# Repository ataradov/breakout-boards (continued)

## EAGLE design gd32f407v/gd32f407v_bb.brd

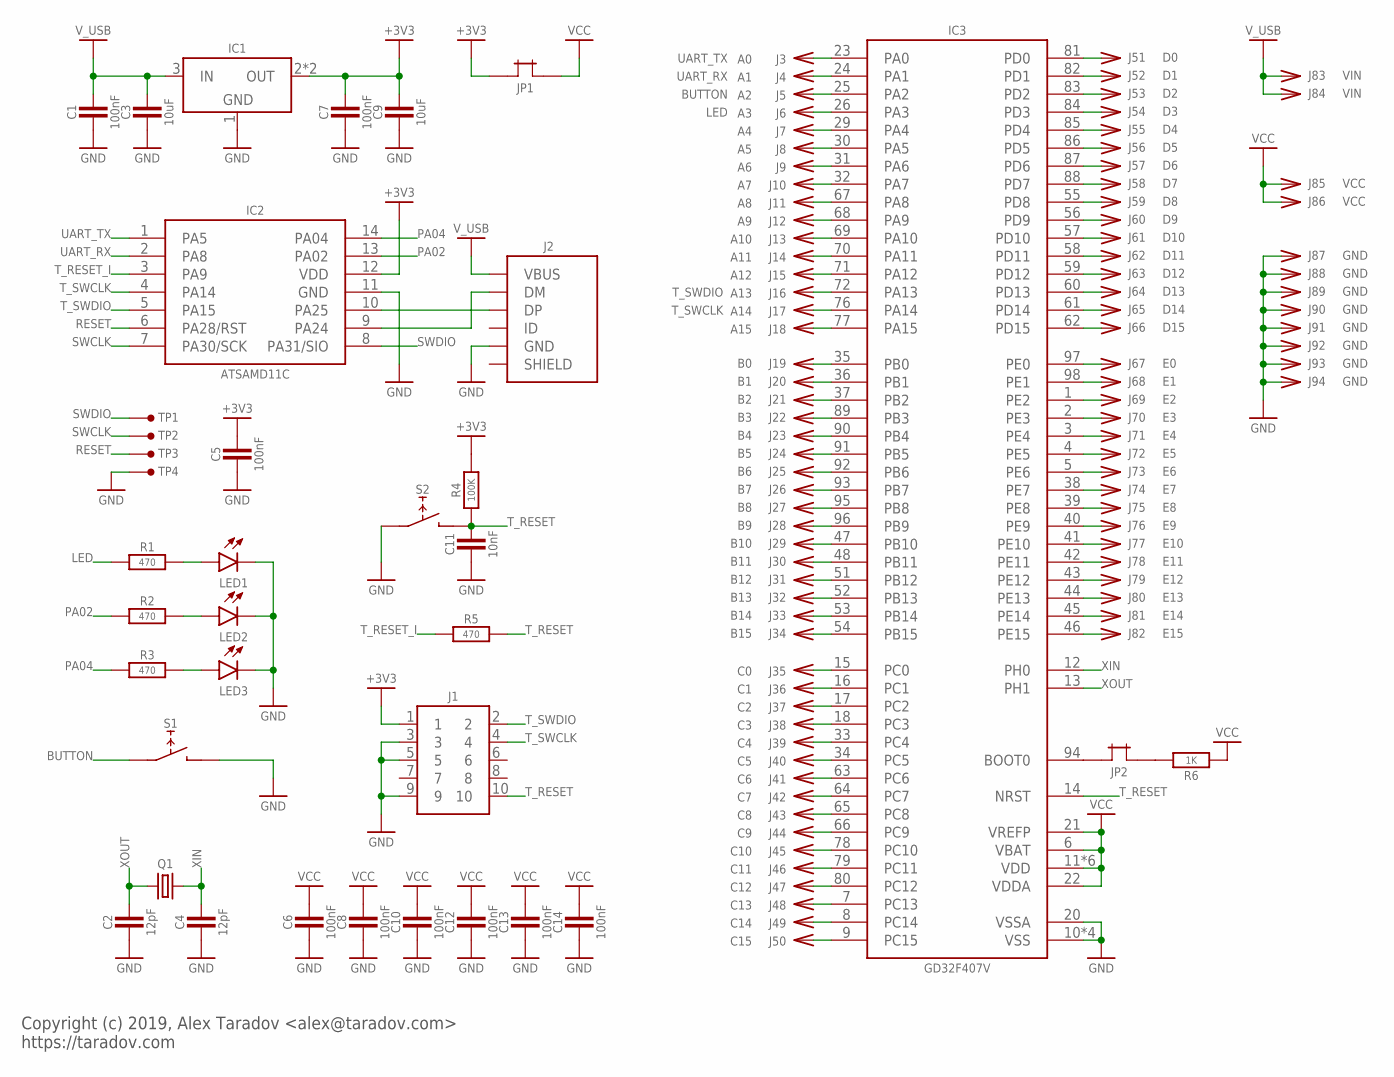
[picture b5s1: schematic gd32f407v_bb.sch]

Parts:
C1, C5, C6, C7, C8, C10, C12, C13, C14: 100nF; SMD0603
C2, C4: 12pF; SMD0603
C3, C9: 10uF; SMD0805
C11: 10nF; SMD0603
IC1: LM1117-SOT223; SOT223
IC2: ATSAMD11C; SO-14
IC3: GD32F407V; TQFP-100-0.5MM
J1: HEADER-5X2-TH-1.27; HEADER-5X2-1.27MM
J2: USB-B-MICRO-SMT; USB-B-MICRO-SMT-SHELL-TH
J3: A0; PIN-TH
J4: A1; PIN-TH
J5: A2; PIN-TH
J6: A3; PIN-TH
J7: A4; PIN-TH
J8: A5; PIN-TH
J9: A6; PIN-TH
J10: A7; PIN-TH
J11: A8; PIN-TH
J12: A9; PIN-TH
J13: A10; PIN-TH
J14: A11; PIN-TH
J15: A12; PIN-TH
J16: A13; PIN-TH
J17: A14; PIN-TH
J18: A15; PIN-TH
J19: B0; PIN-TH
J20: B1; PIN-TH
J21: B2; PIN-TH
J22: B3; PIN-TH
J23: B4; PIN-TH
J24: B5; PIN-TH
J25: B6; PIN-TH
J26: B7; PIN-TH
J27: B8; PIN-TH
J28: B9; PIN-TH
J29: B10; PIN-TH
J30: B11; PIN-TH
J31: B12; PIN-TH
J32: B13; PIN-TH
J33: B14; PIN-TH
J34: B15; PIN-TH
J35: C0; PIN-TH
J36: C1; PIN-TH
J37: C2; PIN-TH
J38: C3; PIN-TH
J39: C4; PIN-TH
J40: C5; PIN-TH
J41: C6; PIN-TH
J42: C7; PIN-TH
J43: C8; PIN-TH
J44: C9; PIN-TH
J45: C10; PIN-TH
J46: C11; PIN-TH
J47: C12; PIN-TH
J48: C13; PIN-TH
J49: C14; PIN-TH
J50: C15; PIN-TH
J51: D0; PIN-TH
J52: D1; PIN-TH
J53: D2; PIN-TH
J54: D3; PIN-TH
J55: D4; PIN-TH
J56: D5; PIN-TH
J57: D6; PIN-TH
J58: D7; PIN-TH
J59: D8; PIN-TH
J60: D9; PIN-TH
J61: D10; PIN-TH
J62: D11; PIN-TH
J63: D12; PIN-TH
J64: D13; PIN-TH
J65: D14; PIN-TH
J66: D15; PIN-TH
J67: E0; PIN-TH
J68: E1; PIN-TH
J69: E2; PIN-TH
J70: E3; PIN-TH
J71: E4; PIN-TH
J72: E5; PIN-TH
J73: E6; PIN-TH
J74: E7; PIN-TH
J75: E8; PIN-TH
J76: E9; PIN-TH
J77: E10; PIN-TH
J78: E11; PIN-TH
J79: E12; PIN-TH
J80: E13; PIN-TH
J81: E14; PIN-TH
J82: E15; PIN-TH
J83, J84: VIN; PIN-TH
J85, J86: VCC; PIN-TH
J87, J88, J89, J90, J91, J92, J93, J94: GND; PIN-TH
JP1, JP2: JUMPER-TH-TH; JUMPER-TH
LED1, LED2, LED3: LED_SMDLED_0603; SMD0603
Q1: XTAL-CTS406; CTS406
R1, R2, R3, R5: 470; SMD0603
R4: 100K; SMD0603
R6: 1K; SMD0603
S1, S2: TACT_SWITCH_6MM-SMD-HALF; TACT-SMD-6MM-HALF
TP1: SIO; TP-1.27MM
TP2, TP3, TP4: TEST-POINT-1.27MM; TP-1.27MM

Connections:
+3V3: C5.2, C7.2, C9.2, IC1.2 (OUT), IC1.4 (OUT), IC2.12 (VDD), J1.1, JP1.1, R4.2
BUTTON: IC3.25 (PA2), J5.1, S1.1
GND: C1.1, C2.1, C3.1, C4.1, C5.1, C6.1, C7.1, C8.1, C9.1, C10.1, C11.1, C12.1, C13.1, C14.1, IC1.1 (GND), IC2.11 (GND), IC3.10 (VSS), IC3.20 (VSSA), IC3.27 (VSS), IC3.74 (VSS), IC3.99 (VSS), J1.3, J1.5, J1.9, J2.5 (GND), J87.1, J88.1, J89.1, J90.1, J91.1, J92.1, J93.1, J94.1, LED1.2 (C), LED2.2 (C), LED3.2 (C), S1.2, S2.1, TP4.1
LED: IC3.26 (PA3), J6.1, R1.1
unnamed: IC2.9 (PA24), J2.2 (DM)
unnamed: IC2.10 (PA25), J2.3 (DP)
unnamed: LED2.1 (A), R2.2
unnamed: LED3.1 (A), R3.2
unnamed: IC3.29 (PA4), J7.1
unnamed: IC3.30 (PA5), J8.1
unnamed: IC3.31 (PA6), J9.1
unnamed: IC3.32 (PA7), J10.1
unnamed: IC3.67 (PA8), J11.1
unnamed: IC3.68 (PA9), J12.1
unnamed: IC3.69 (PA10), J13.1
unnamed: IC3.70 (PA11), J14.1
unnamed: IC3.71 (PA12), J15.1
unnamed: IC3.77 (PA15), J18.1
unnamed: IC3.81 (PD0), J51.1
unnamed: IC3.82 (PD1), J52.1
unnamed: IC3.83 (PD2), J53.1
unnamed: IC3.84 (PD3), J54.1
unnamed: IC3.85 (PD4), J55.1
unnamed: IC3.86 (PD5), J56.1
unnamed: IC3.87 (PD6), J57.1
unnamed: IC3.88 (PD7), J58.1
unnamed: IC3.55 (PD8), J59.1
unnamed: IC3.56 (PD9), J60.1
unnamed: IC3.57 (PD10), J61.1
unnamed: IC3.58 (PD11), J62.1
unnamed: IC3.59 (PD12), J63.1
unnamed: IC3.60 (PD13), J64.1
unnamed: IC3.61 (PD14), J65.1
unnamed: IC3.62 (PD15), J66.1
unnamed: IC3.35 (PB0), J19.1
unnamed: IC3.36 (PB1), J20.1
unnamed: IC3.37 (PB2), J21.1
unnamed: IC3.89 (PB3), J22.1
unnamed: IC3.90 (PB4), J23.1
unnamed: IC3.91 (PB5), J24.1
unnamed: IC3.92 (PB6), J25.1
unnamed: IC3.93 (PB7), J26.1
unnamed: IC3.95 (PB8), J27.1
unnamed: IC3.96 (PB9), J28.1
unnamed: IC3.47 (PB10), J29.1
unnamed: IC3.48 (PB11), J30.1
unnamed: IC3.51 (PB12), J31.1
unnamed: LED1.1 (A), R1.2
unnamed: IC3.52 (PB13), J32.1
unnamed: IC3.53 (PB14), J33.1
unnamed: IC3.54 (PB15), J34.1
unnamed: IC3.97 (PE0), J67.1
unnamed: IC3.98 (PE1), J68.1
unnamed: IC3.1 (PE2), J69.1
unnamed: IC3.2 (PE3), J70.1
unnamed: IC3.3 (PE4), J71.1
unnamed: IC3.4 (PE5), J72.1
unnamed: IC3.5 (PE6), J73.1
unnamed: IC3.38 (PE7), J74.1
unnamed: IC3.39 (PE8), J75.1
unnamed: IC3.40 (PE9), J76.1
unnamed: IC3.41 (PE10), J77.1
unnamed: IC3.42 (PE11), J78.1
unnamed: IC3.43 (PE12), J79.1
unnamed: IC3.44 (PE13), J80.1
unnamed: IC3.45 (PE14), J81.1
unnamed: IC3.46 (PE15), J82.1
unnamed: IC3.15 (PC0), J35.1
unnamed: IC3.16 (PC1), J36.1
unnamed: IC3.17 (PC2), J37.1
unnamed: IC3.18 (PC3), J38.1
unnamed: IC3.33 (PC4), J39.1
unnamed: IC3.34 (PC5), J40.1
unnamed: IC3.63 (PC6), J41.1
unnamed: IC3.64 (PC7), J42.1
unnamed: IC3.65 (PC8), J43.1
unnamed: IC3.66 (PC9), J44.1
unnamed: IC3.78 (PC10), J45.1
unnamed: IC3.79 (PC11), J46.1
unnamed: IC3.80 (PC12), J47.1
unnamed: IC3.7 (PC13), J48.1
unnamed: IC3.8 (PC14), J49.1
unnamed: IC3.9 (PC15), J50.1
unnamed: IC3.94 (BOOT0), JP2.1
unnamed: JP2.2, R6.2
PA02: IC2.13 (PA02), R2.1
PA04: IC2.14 (PA04), R3.1
RESET: IC2.6 (PA28/RST), TP3.1
SWCLK: IC2.7 (PA30/SCK), TP2.1
SWDIO: IC2.8 (PA31/SIO), TP1.1
T_RESET: C11.2, IC3.14 (NRST), J1.10, R4.1, R5.2, S2.2
T_RESET_I: IC2.3 (PA9), R5.1
T_SWCLK: IC2.4 (PA14), IC3.76 (PA14), J1.4, J17.1
T_SWDIO: IC2.5 (PA15), IC3.72 (PA13), J1.2, J16.1
UART_RX: IC2.2 (PA8), IC3.24 (PA1), J4.1
UART_TX: IC2.1 (PA5), IC3.23 (PA0), J3.1
VCC: C6.2, C8.2, C10.2, C12.2, C13.2, C14.2, IC3.6 (VBAT), IC3.11 (VDD), IC3.19 (VDD), IC3.21 (VREFP), IC3.22 (VDDA), IC3.28 (VDD), IC3.50 (VDD), IC3.75 (VDD), IC3.100 (VDD), J85.1, J86.1, JP1.2, R6.1
V_USB: C1.2, C3.2, IC1.3 (IN), J2.1 (VBUS), J83.1, J84.1
XIN: C4.2, IC3.12 (PH0), Q1.3 (2)
XOUT: C2.2, IC3.13 (PH1), Q1.1

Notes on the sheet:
Copyright (c) 2019, Alex Taradov <alex@taradov.com> https://taradov.com

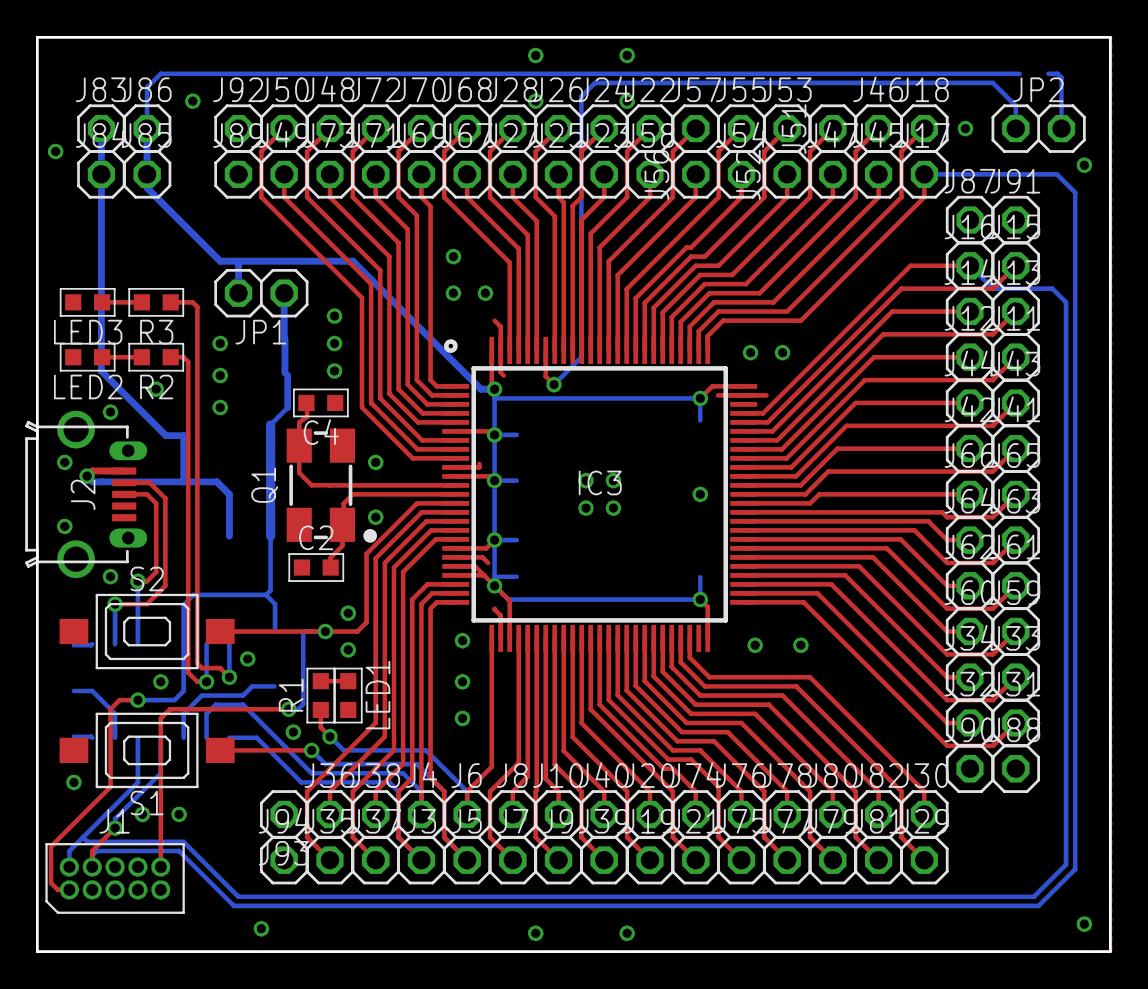
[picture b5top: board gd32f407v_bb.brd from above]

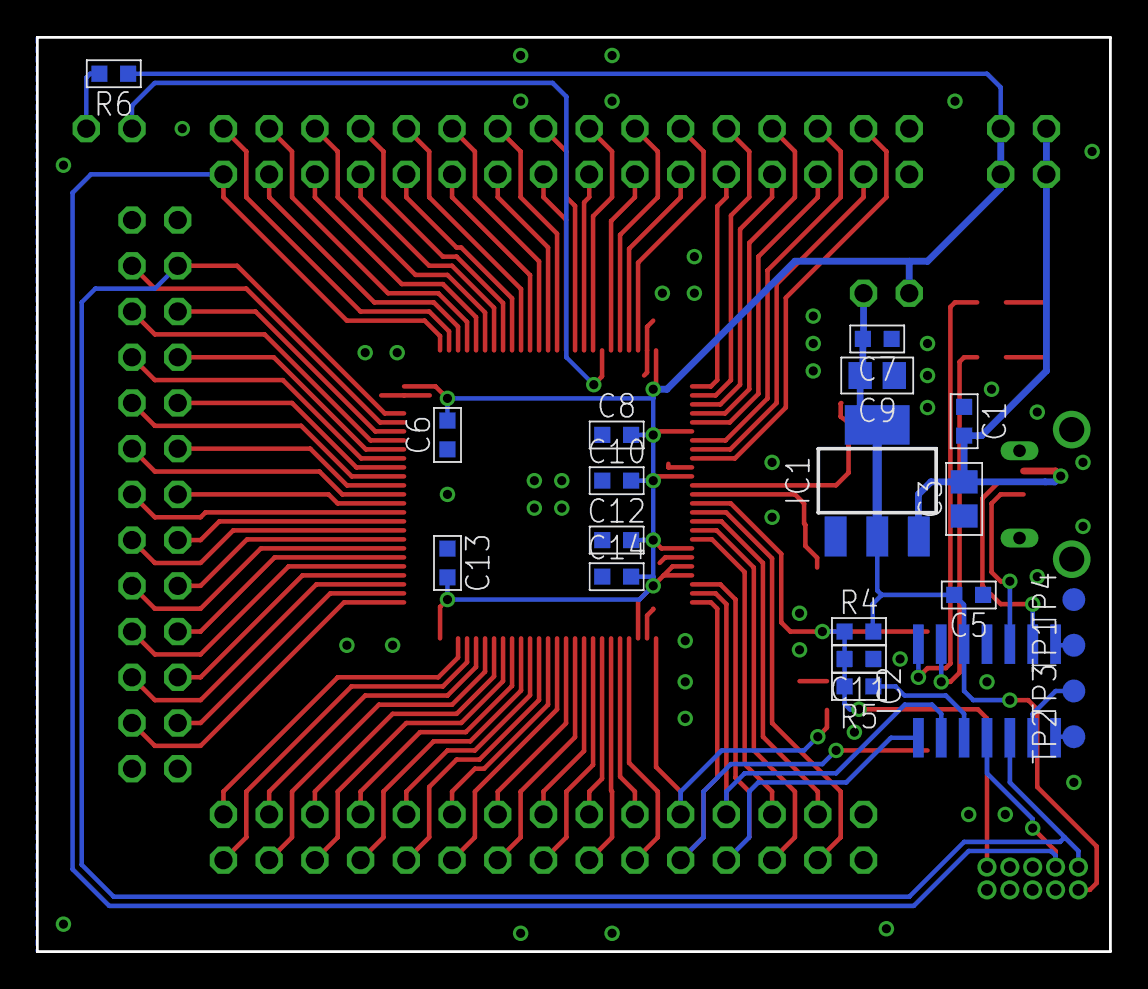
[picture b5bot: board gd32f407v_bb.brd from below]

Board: 2 copper layers, 59.6 x 50.8 mm, 129 parts (21 on the bottom side), 100 nets.

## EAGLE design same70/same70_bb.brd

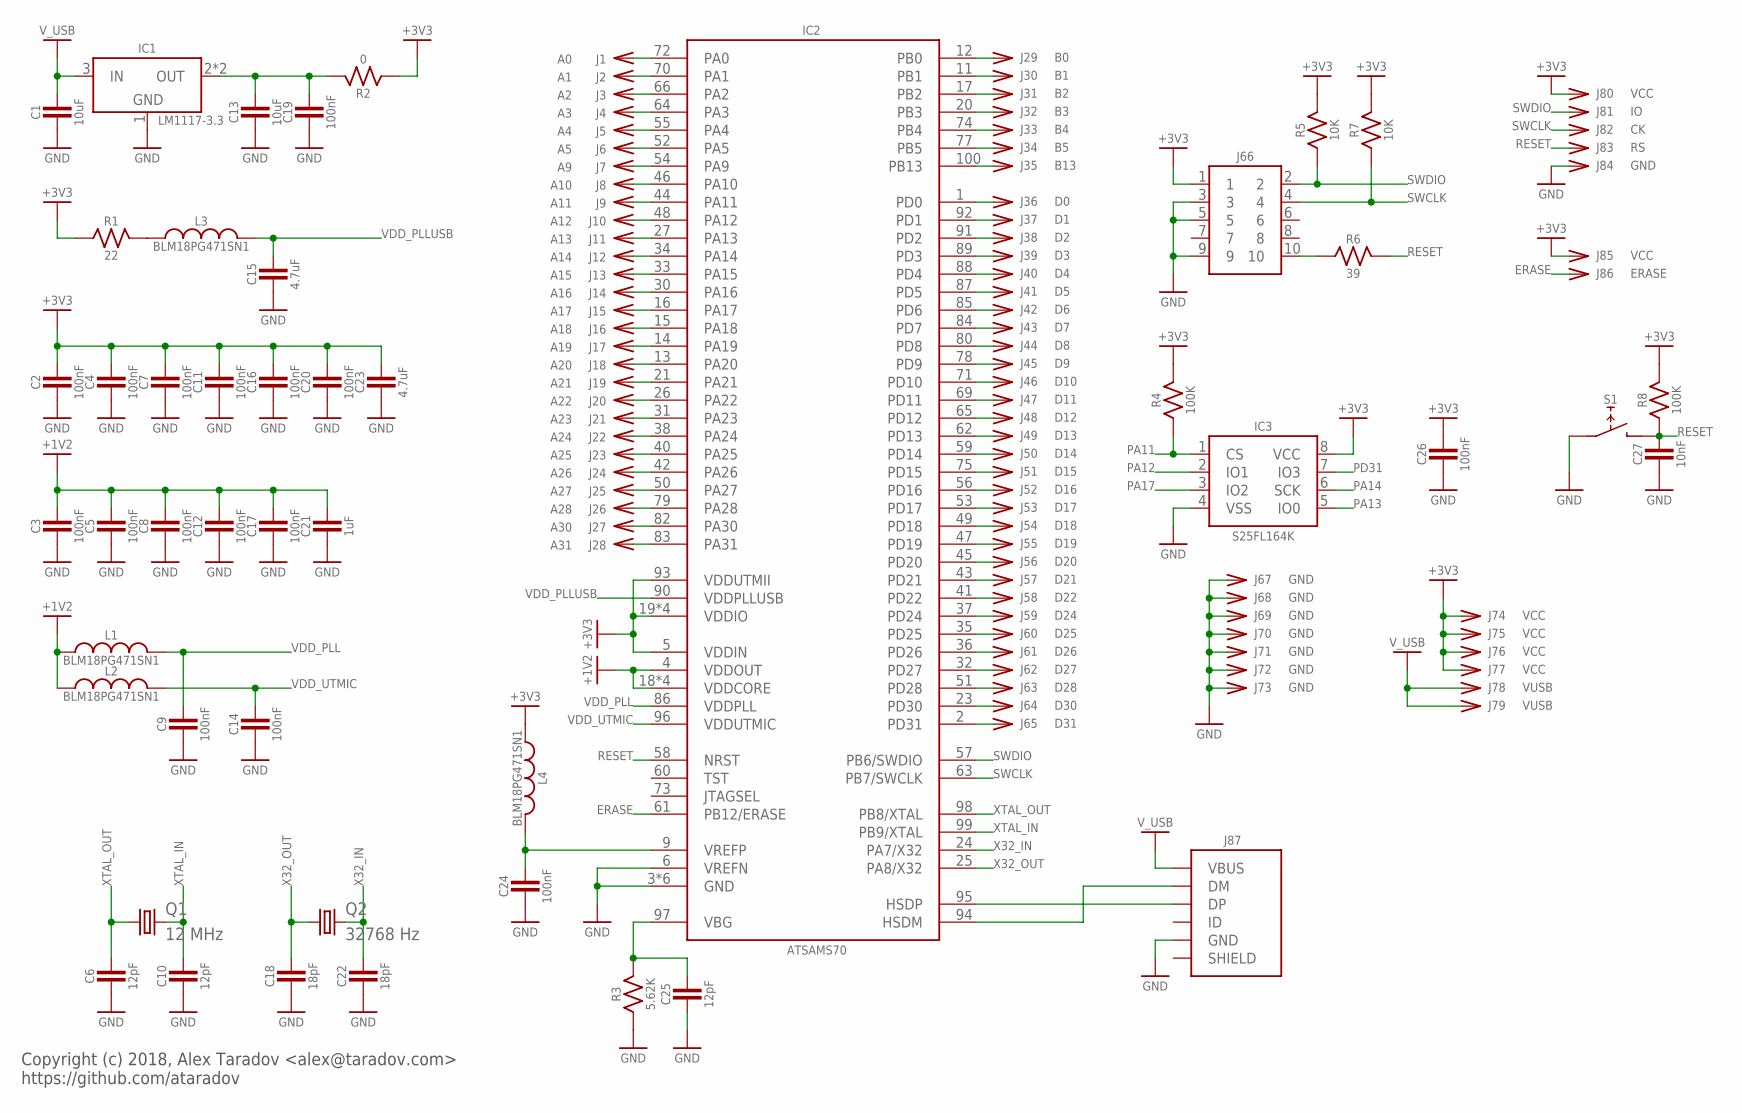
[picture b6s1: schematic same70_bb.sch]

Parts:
C1, C13: 10uF; SMD0805
C2, C3, C4, C5, C7, C8, C9, C11, C12, C14, C16, C17, C19, C20, C24, C26: 100nF; SMD0603
C6, C10, C25: 12pF; SMD0603
C15, C23: 4.7uF; SMD0603
C18, C22: 18pF; SMD0603
C21: 1uF; SMD0603
C27: 10nF; SMD0603
IC1: LM1117-3.3; SOT223
IC2: ATSAMS70; TQFP-100-0.5MM
IC3: S25FL164K; SO8
J1: A0; PIN-TH
J2: A1; PIN-TH
J3: A2; PIN-TH
J4: A3; PIN-TH
J5: A4; PIN-TH
J6: A5; PIN-TH
J7: A9; PIN-TH
J8: A10; PIN-TH
J9: A11; PIN-TH
J10: A12; PIN-TH
J11: A13; PIN-TH
J12: A14; PIN-TH
J13: A15; PIN-TH
J14: A16; PIN-TH
J15: A17; PIN-TH
J16: A18; PIN-TH
J17: A19; PIN-TH
J18: A20; PIN-TH
J19: A21; PIN-TH
J20: A22; PIN-TH
J21: A23; PIN-TH
J22: A24; PIN-TH
J23: A25; PIN-TH
J24: A26; PIN-TH
J25: A27; PIN-TH
J26: A28; PIN-TH
J27: A30; PIN-TH
J28: A31; PIN-TH
J29: B0; PIN-TH
J30: B1; PIN-TH
J31: B2; PIN-TH
J32: B3; PIN-TH
J33: B4; PIN-TH
J34: B5; PIN-TH
J35: B13; PIN-TH
J36: D0; PIN-TH
J37: D1; PIN-TH
J38: D2; PIN-TH
J39: D3; PIN-TH
J40: D4; PIN-TH
J41: D5; PIN-TH
J42: D6; PIN-TH
J43: D7; PIN-TH
J44: D8; PIN-TH
J45: D9; PIN-TH
J46: D10; PIN-TH
J47: D11; PIN-TH
J48: D12; PIN-TH
J49: D13; PIN-TH
J50: D14; PIN-TH
J51: D15; PIN-TH
J52: D16; PIN-TH
J53: D17; PIN-TH
J54: D18; PIN-TH
J55: D19; PIN-TH
J56: D20; PIN-TH
J57: D21; PIN-TH
J58: D22; PIN-TH
J59: D24; PIN-TH
J60: D25; PIN-TH
J61: D26; PIN-TH
J62: D27; PIN-TH
J63: D28; PIN-TH
J64: D30; PIN-TH
J65: D31; PIN-TH
J66: HEADER-5X2-TH-1.27; HEADER-5X2-1.27MM
J67, J68, J69, J70, J71, J72, J73, J84: GND; PIN-TH
J74, J75, J76, J77, J80, J85: VCC; PIN-TH
J78, J79: VUSB; PIN-TH
J81: IO; PIN-TH
J82: CK; PIN-TH
J83: RS; PIN-TH
J86: ERASE; PIN-TH
J87: USB-B-MICRO-SMT; USB-B-MICRO-SMT-SHELL-TH
L1, L2, L3, L4: BLM18PG471SN1; SMD0603
Q1: 12 MHz; CTS406
Q2: 32768 Hz; TC38H
R1: 22; SMD0603
R2: 0; SMD0603
R3: 5.62K; SMD0603
R4, R8: 100K; SMD0603
R5, R7: 10K; SMD0603
R6: 39; SMD0603
S1: TACT_SWITCH_6MM-SMD; TACT-SMD-6MM

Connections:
+1V2: C3.2, C5.2, C8.2, C12.2, C17.2, C21.2, IC2.4 (VDDOUT), IC2.18 (VDDCORE), IC2.22 (VDDCORE), IC2.39 (VDDCORE), IC2.76 (VDDCORE), L1.1, L2.1
+3V3: C2.2, C4.2, C7.2, C11.2, C16.2, C20.2, C23.2, C26.2, IC2.5 (VDDIN), IC2.19 (VDDIO), IC2.28 (VDDIO), IC2.68 (VDDIO), IC2.81 (VDDIO), IC2.93 (VDDUTMII), IC3.8 (VCC), J66.1, J74.1, J75.1, J76.1, J77.1, J80.1, J85.1, L4.1, R1.1, R2.1, R4.2, R5.2, R7.2, R8.2
ERASE: IC2.61 (PB12/ERASE), J86.1
GND: C1.1, C2.1, C3.1, C4.1, C5.1, C6.1, C7.1, C8.1, C9.1, C10.1, C11.1, C12.1, C13.1, C14.1, C15.1, C16.1, C17.1, C18.1, C19.1, C20.1, C21.1, C22.1, C23.1, C24.1, C25.1, C26.1, C27.1, IC1.1 (GND), IC2.3 (GND), IC2.6 (VREFN), IC2.7 (GND), IC2.8 (GND), IC2.10 (GND), IC2.29 (GND), IC2.67 (GND), IC3.4 (VSS), J66.3, J66.5, J66.9, J67.1, J68.1, J69.1, J70.1, J71.1, J72.1, J73.1, J84.1, J87.5 (GND), R3.1, S1.1, S1.2 (1)
unnamed: IC2.45 (PD20), J56.1
unnamed: J66.10, R6.1
unnamed: IC2.12 (PB0), J29.1
unnamed: IC2.11 (PB1), J30.1
unnamed: IC2.17 (PB2), J31.1
unnamed: IC2.20 (PB3), J32.1
unnamed: IC2.74 (PB4), J33.1
unnamed: IC2.77 (PB5), J34.1
unnamed: IC2.89 (PD3), J39.1
unnamed: IC2.47 (PD19), J55.1
unnamed: IC2.49 (PD18), J54.1
unnamed: IC2.53 (PD17), J53.1
unnamed: IC2.100 (PB13), J35.1
unnamed: IC2.1 (PD0), J36.1
unnamed: IC2.92 (PD1), J37.1
unnamed: IC2.91 (PD2), J38.1
unnamed: IC2.56 (PD16), J52.1
unnamed: IC2.75 (PD15), J51.1
unnamed: IC2.59 (PD14), J50.1
unnamed: IC2.62 (PD13), J49.1
unnamed: IC2.65 (PD12), J48.1
unnamed: IC2.69 (PD11), J47.1
unnamed: IC2.71 (PD10), J46.1
unnamed: IC2.78 (PD9), J45.1
unnamed: IC2.80 (PD8), J44.1
unnamed: IC2.84 (PD7), J43.1
unnamed: IC2.23 (PD30), J64.1
unnamed: IC2.51 (PD28), J63.1
unnamed: IC2.32 (PD27), J62.1
unnamed: IC2.36 (PD26), J61.1
unnamed: IC2.35 (PD25), J60.1
unnamed: IC2.37 (PD24), J59.1
unnamed: IC2.41 (PD22), J58.1
unnamed: IC2.43 (PD21), J57.1
unnamed: IC2.85 (PD6), J42.1
unnamed: IC2.72 (PA0), J1.1
unnamed: IC2.70 (PA1), J2.1
unnamed: IC2.66 (PA2), J3.1
unnamed: IC2.64 (PA3), J4.1
unnamed: IC2.55 (PA4), J5.1
unnamed: IC2.52 (PA5), J6.1
unnamed: IC2.54 (PA9), J7.1
unnamed: IC2.46 (PA10), J8.1
unnamed: IC2.88 (PD4), J40.1
unnamed: IC2.87 (PD5), J41.1
unnamed: IC2.33 (PA15), J13.1
unnamed: IC2.30 (PA16), J14.1
unnamed: IC2.15 (PA18), J16.1
unnamed: IC2.14 (PA19), J17.1
unnamed: IC2.13 (PA20), J18.1
unnamed: IC2.21 (PA21), J19.1
unnamed: IC2.26 (PA22), J20.1
unnamed: IC2.31 (PA23), J21.1
unnamed: IC2.38 (PA24), J22.1
unnamed: IC2.42 (PA26), J24.1
unnamed: IC2.50 (PA27), J25.1
unnamed: IC2.79 (PA28), J26.1
unnamed: IC2.82 (PA30), J27.1
unnamed: IC2.83 (PA31), J28.1
unnamed: IC2.40 (PA25), J23.1
unnamed: C25.2, IC2.97 (VBG), R3.2
unnamed: IC2.94 (HSDM), J87.2 (DM)
unnamed: C24.2, IC2.9 (VREFP), L4.2
unnamed: C13.2, C19.2, IC1.2 (OUT), IC1.4 (OUT), R2.2
unnamed: IC2.95 (HSDP), J87.3 (DP)
unnamed: L3.1, R1.2
PA11: IC2.44 (PA11), IC3.1 (CS), J9.1, R4.1
PA12: IC2.48 (PA12), IC3.2 (IO1), J10.1
PA13: IC2.27 (PA13), IC3.5 (IO0), J11.1
PA14: IC2.34 (PA14), IC3.6 (SCK), J12.1
PA17: IC2.16 (PA17), IC3.3 (IO2), J15.1
PD31: IC2.2 (PD31), IC3.7 (IO3), J65.1
RESET: C27.2, IC2.58 (NRST), J83.1, R6.2, R8.1, S1.3 (2), S1.4 (2)
SWCLK: IC2.63 (PB7/SWCLK), J66.4, J82.1, R7.1
SWDIO: IC2.57 (PB6/SWDIO), J66.2, J81.1, R5.1
VDD_PLL: C9.2, IC2.86 (VDDPLL), L1.2
VDD_PLLUSB: C15.2, IC2.90 (VDDPLLUSB), L3.2
VDD_UTMIC: C14.2, IC2.96 (VDDUTMIC), L2.2
V_USB: C1.2, IC1.3 (IN), J78.1, J79.1, J87.1 (VBUS)
X32_IN: C22.2, IC2.24 (PA7/X32), Q2.2
X32_OUT: C18.2, IC2.25 (PA8/X32), Q2.1
XTAL_IN: C10.2, IC2.99 (PB9/XTAL), Q1.3 (2)
XTAL_OUT: C6.2, IC2.98 (PB8/XTAL), Q1.1

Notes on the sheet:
Copyright (c) 2018, Alex Taradov <alex@taradov.com> https://github.com/ataradov

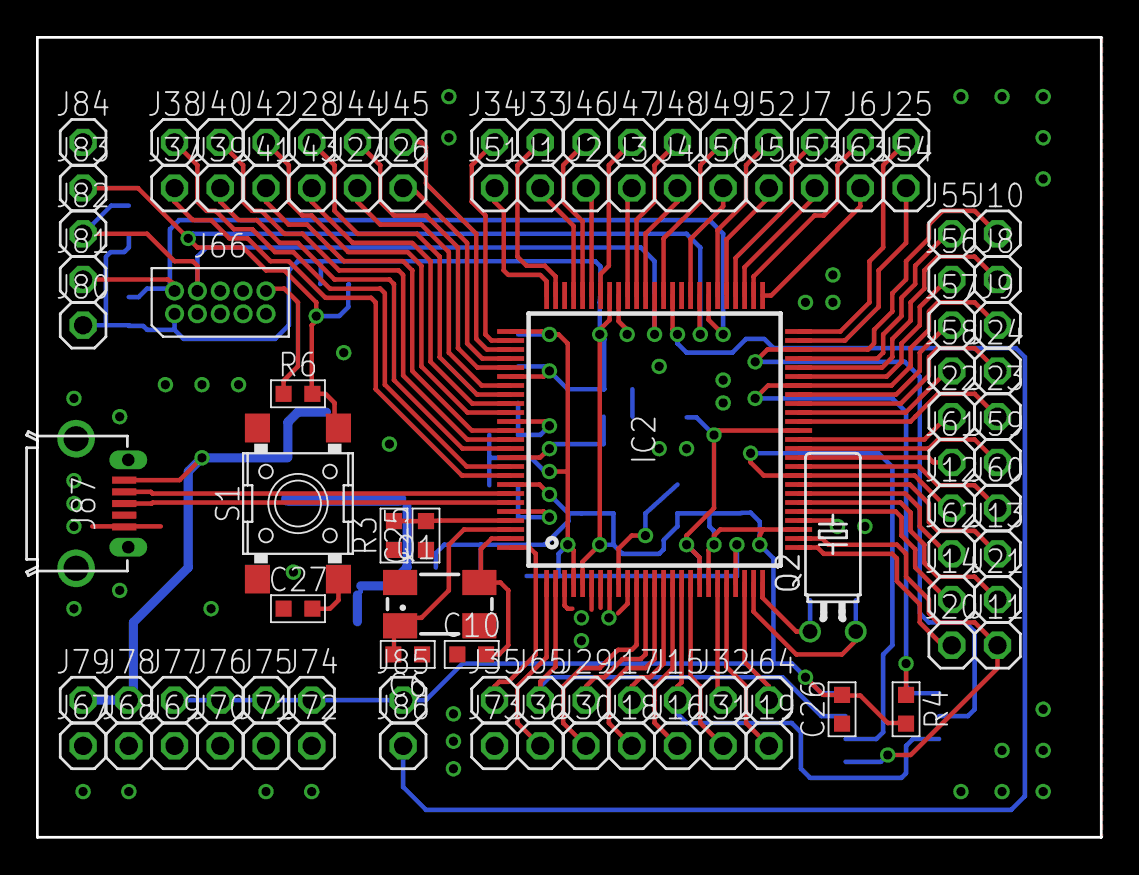
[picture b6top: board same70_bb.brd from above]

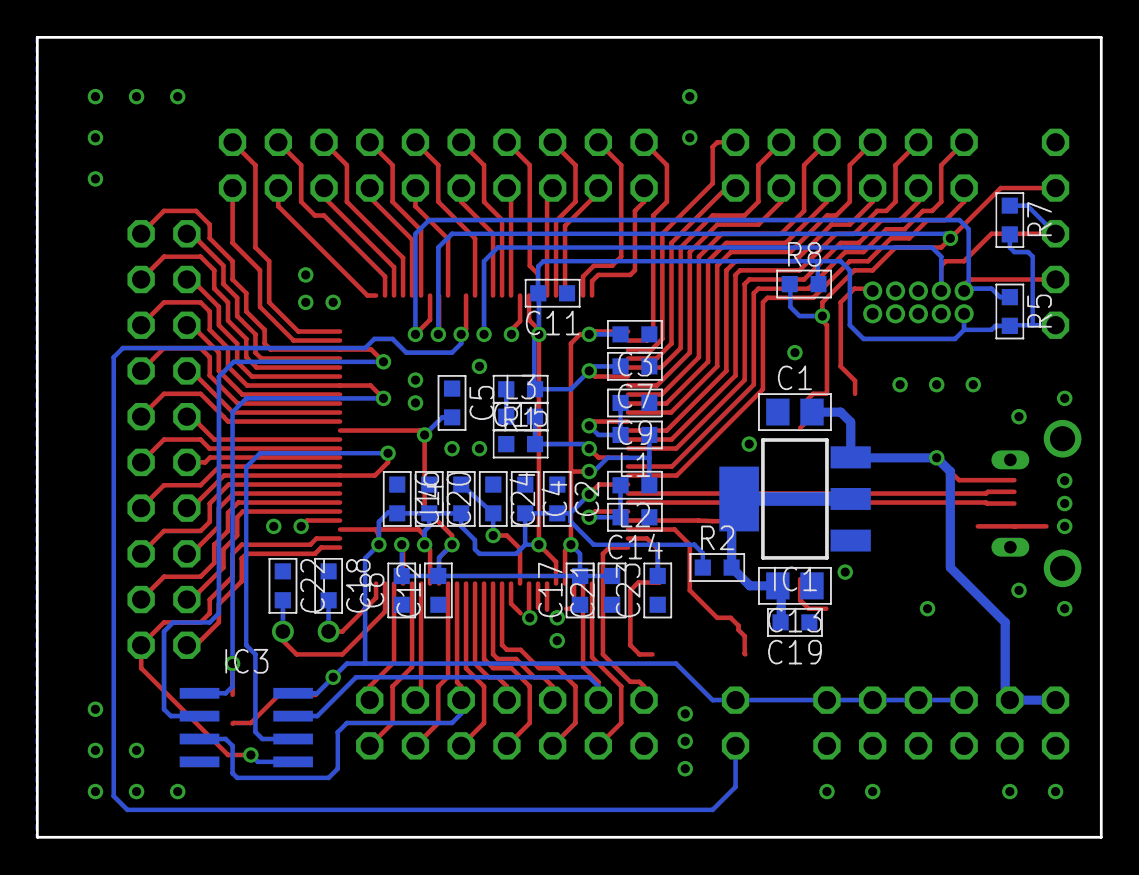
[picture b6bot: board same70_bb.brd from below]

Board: 2 copper layers, 59.1 x 44.4 mm, 132 parts (33 on the bottom side), 87 nets.

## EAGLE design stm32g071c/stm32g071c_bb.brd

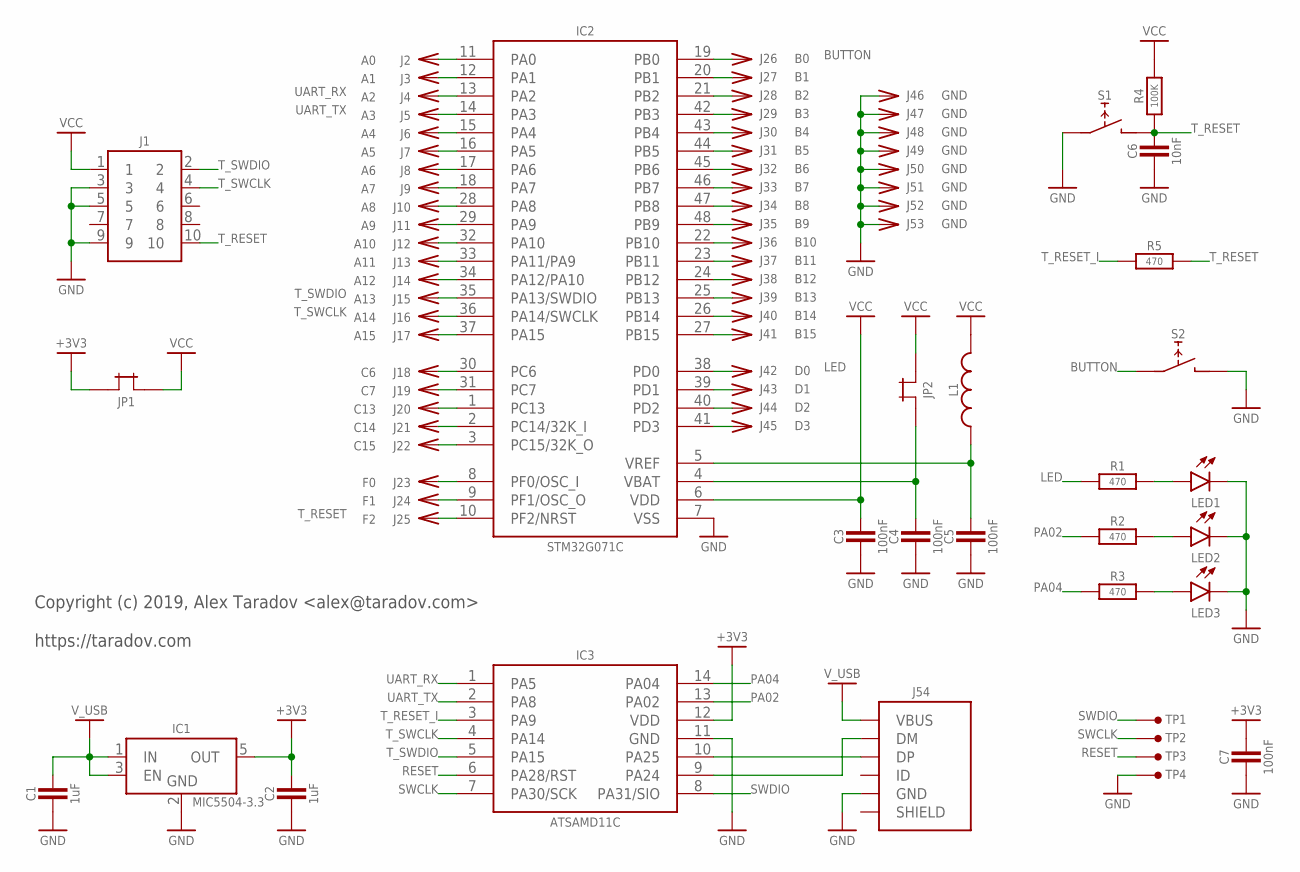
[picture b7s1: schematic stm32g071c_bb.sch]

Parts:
C1, C2: 1uF; SMD0603
C3, C4, C5, C7: 100nF; SMD0603
C6: 10nF; SMD0603
IC1: MIC5504-3.3; SOT23-5
IC2: STM32G071C; TQFP-48-0.5MM
IC3: ATSAMD11C; SO-14
J1: HEADER-5X2-TH-1.27; HEADER-5X2-1.27MM
J2: A0; PIN-TH
J3: A1; PIN-TH
J4: A2; PIN-TH
J5: A3; PIN-TH
J6: A4; PIN-TH
J7: A5; PIN-TH
J8: A6; PIN-TH
J9: A7; PIN-TH
J10: A8; PIN-TH
J11: A9; PIN-TH
J12: A10; PIN-TH
J13: A11; PIN-TH
J14: A12; PIN-TH
J15: A13; PIN-TH
J16: A14; PIN-TH
J17: A15; PIN-TH
J18: C6; PIN-TH
J19: C7; PIN-TH
J20: C13; PIN-TH
J21: C14; PIN-TH
J22: C15; PIN-TH
J23: F0; PIN-TH
J24: F1; PIN-TH
J25: F2; PIN-TH
J26: B0; PIN-TH
J27: B1; PIN-TH
J28: B2; PIN-TH
J29: B3; PIN-TH
J30: B4; PIN-TH
J31: B5; PIN-TH
J32: B6; PIN-TH
J33: B7; PIN-TH
J34: B8; PIN-TH
J35: B9; PIN-TH
J36: B10; PIN-TH
J37: B11; PIN-TH
J38: B12; PIN-TH
J39: B13; PIN-TH
J40: B14; PIN-TH
J41: B15; PIN-TH
J42: D0; PIN-TH
J43: D1; PIN-TH
J44: D2; PIN-TH
J45: D3; PIN-TH
J46, J47, J48, J49, J50, J51, J52, J53: GND; PIN-TH
J54: USB-B-MICRO-SMT; USB-B-MICRO-SMT-SHELL-TH
JP1, JP2: JUMPER-TH-TH; JUMPER-TH
L1: L-0603; SMD0603
LED1, LED2, LED3: LED_SMDLED_0603; SMD0603
R1, R2, R3, R5: 470; SMD0603
R4: 100K; SMD0603
S1, S2: TACT_SWITCH_6MM-SMD-HALF; TACT-SMD-6MM-HALF
TP1: SIO; TP-1.27MM
TP2, TP3, TP4: TEST-POINT-1.27MM; TP-1.27MM

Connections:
+3V3: C2.2, C7.2, IC1.5 (OUT), IC3.12 (VDD), JP1.1
BUTTON: IC2.19 (PB0), J26.1, S2.1
GND: C1.1, C2.1, C3.1, C4.1, C5.1, C6.1, C7.1, IC1.2 (GND), IC2.7 (VSS), IC3.11 (GND), J1.3, J1.5, J1.9, J46.1, J47.1, J48.1, J49.1, J50.1, J51.1, J52.1, J53.1, J54.5 (GND), LED1.2 (C), LED2.2 (C), LED3.2 (C), S1.1, S2.2, TP4.1
LED: IC2.38 (PD0), J42.1, R1.1
unnamed: IC3.9 (PA24), J54.2 (DM)
unnamed: IC3.10 (PA25), J54.3 (DP)
unnamed: LED2.1 (A), R2.2
unnamed: IC2.20 (PB1), J27.1
unnamed: LED3.1 (A), R3.2
unnamed: IC2.21 (PB2), J28.1
unnamed: IC2.42 (PB3), J29.1
unnamed: IC2.43 (PB4), J30.1
unnamed: IC2.45 (PB6), J32.1
unnamed: IC2.47 (PB8), J34.1
unnamed: IC2.48 (PB9), J35.1
unnamed: IC2.22 (PB10), J36.1
unnamed: IC2.23 (PB11), J37.1
unnamed: IC2.24 (PB12), J38.1
unnamed: IC2.25 (PB13), J39.1
unnamed: IC2.26 (PB14), J40.1
unnamed: IC2.27 (PB15), J41.1
unnamed: IC2.44 (PB5), J31.1
unnamed: IC2.46 (PB7), J33.1
unnamed: IC2.11 (PA0), J2.1
unnamed: IC2.12 (PA1), J3.1
unnamed: IC2.15 (PA4), J6.1
unnamed: IC2.16 (PA5), J7.1
unnamed: IC2.17 (PA6), J8.1
unnamed: IC2.18 (PA7), J9.1
unnamed: IC2.28 (PA8), J10.1
unnamed: IC2.29 (PA9), J11.1
unnamed: IC2.32 (PA10), J12.1
unnamed: IC2.33 (PA11/PA9), J13.1
unnamed: IC2.34 (PA12/PA10), J14.1
unnamed: IC2.37 (PA15), J17.1
unnamed: IC2.39 (PD1), J43.1
unnamed: IC2.41 (PD3), J45.1
unnamed: IC2.40 (PD2), J44.1
unnamed: IC2.30 (PC6), J18.1
unnamed: IC2.1 (PC13), J20.1
unnamed: IC2.2 (PC14/32K_I), J21.1
unnamed: IC2.3 (PC15/32K_O), J22.1
unnamed: IC2.9 (PF1/OSC_O), J24.1
unnamed: IC2.8 (PF0/OSC_I), J23.1
unnamed: IC2.31 (PC7), J19.1
unnamed: C5.2, IC2.5 (VREF), L1.1
unnamed: C4.2, IC2.4 (VBAT), JP2.1
unnamed: LED1.1 (A), R1.2
PA02: IC3.13 (PA02), R2.1
PA04: IC3.14 (PA04), R3.1
RESET: IC3.6 (PA28/RST), TP3.1
SWCLK: IC3.7 (PA30/SCK), TP2.1
SWDIO: IC3.8 (PA31/SIO), TP1.1
T_RESET: C6.2, IC2.10 (PF2/NRST), J1.10, J25.1, R4.1, R5.2, S1.2
T_RESET_I: IC3.3 (PA9), R5.1
T_SWCLK: IC2.36 (PA14/SWCLK), IC3.4 (PA14), J1.4, J16.1
T_SWDIO: IC2.35 (PA13/SWDIO), IC3.5 (PA15), J1.2, J15.1
UART_RX: IC2.13 (PA2), IC3.1 (PA5), J4.1
UART_TX: IC2.14 (PA3), IC3.2 (PA8), J5.1
VCC: C3.2, IC2.6 (VDD), J1.1, JP1.2, JP2.2, L1.2, R4.2
V_USB: C1.2, IC1.1 (IN), IC1.3 (EN), J54.1 (VBUS)

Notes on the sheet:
Copyright (c) 2019, Alex Taradov <alex@taradov.com> https://taradov.com

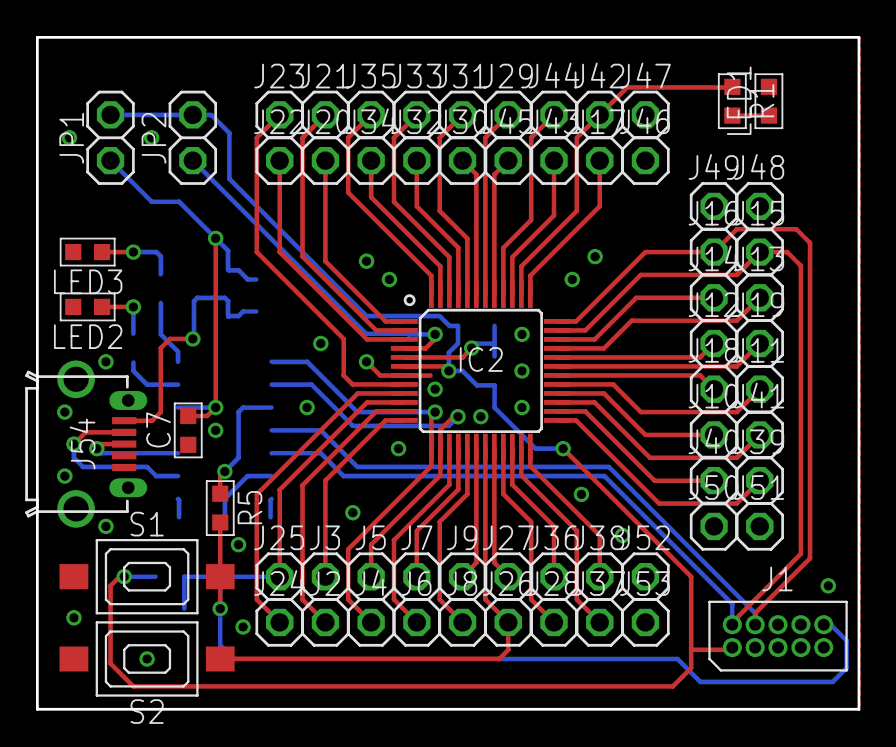
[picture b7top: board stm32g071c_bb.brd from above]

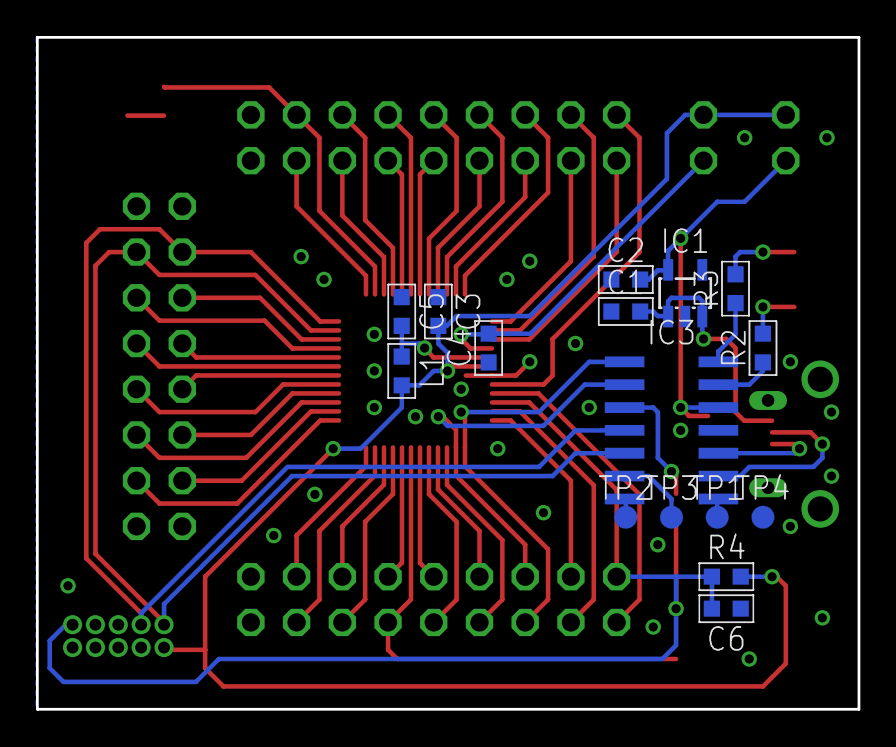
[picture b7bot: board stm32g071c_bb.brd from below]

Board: 2 copper layers, 45.6 x 37.3 mm, 81 parts (16 on the bottom side), 61 nets.

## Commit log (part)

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2019-04-28 Added initial boards
2019-04-28 Added pictures
2019-04-30 Added SAME70 pictures
2019-10-07 Added a board for GD32F407V
2019-12-29 Added boards for Lattice LCMXO256C and LCMXO2-2000HC
2019-12-30 Typos
2020-01-15 Added demo projects for lcmxo2-2000hc and lcmxo256c
2020-01-15 Added pictures for lcmxo2-2000hc and lcmxo256c
2020-12-02 Added Nuvoton M484SIDAE
2021-01-16 Added a small USB test board with a USB A plug
2022-02-18 Added RP2040 board
2022-02-18 Modified readme for the RP2040 board
2022-02-18 Added pictures for RP2040
2025-08-30 Added T20Q100F3 and STM32H7
2025-10-26 Added STM32G441KB board
